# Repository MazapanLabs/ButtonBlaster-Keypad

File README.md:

# ButtonBlaster-Keypad

ButtonBlaster is a compact 48-key keypad based on the Orpheus Pico microcontroller and designed to work with the KMK firmware. The project was inspired by an ergonomic keyboard shown in a video by Joe Scotto. The PCB was custom-designed and paired with a 3D-printed case. It uses Gateron mechanical switches and discrete diodes.

## 🎥 Inspiration

Design inspired by a keyboard featured in a video by Joe Scotto:  
https://youtu.be/sMTs8F6Fk6s?si=EPKrmchUF-LIuJZo

---

## 📦 Specifications

### 🔩 Bill of Materials (BOM)

| Quantity | Component                             | Link                                                                                                     |
|----------|----------------------------------------|----------------------------------------------------------------------------------------------------------|
| 48x      | Gateron KS-3X1 Milky Switch            | [Keychron](https://www.keychron.mx/products/gateron-ks-3x1-milky-switch?variant=45655197909205)         |
| 48x      | Keycaps                                | [Keychron](https://www.keychron.mx/products/keychron-k12-keycap-set?variant=45655109271765)             |
| 48x      | Diodes 1N4148                          | [UElectronics](https://uelectronics.com/producto/kit-de-100-diodos-1n5399-1n5408-1n4148-1n4007-1n5819-1n5822/) |
| 1x       | Orpheus Pico                           | —                                                                                                        |
| 1x       | Custom PCB                             | —                                                                                                        |
| 10x      | M3 brass heatsets                      | [UElectronics](https://uelectronics.com/producto/rosca-de-laton-m2-m3-m4/)                               |
| 10x      | M3x12 screws                           | [MercadoLibre](https://articulo.mercadolibre.com.mx/MLM-3383497816-tornillo-m3-de-cruz-12mm-100pzs-_JM) |

### 🧰 Other files

- Firmware: **KMK**
- STL files:
  - `ButtonBlaster-Keypad_Top.stl`
  - `ButtonBlaster-Keypad_Bottom.stl`

---

## 📷 Project Images

### 🔌 Schematic

### 🧠 PCB

### 🧱 Case

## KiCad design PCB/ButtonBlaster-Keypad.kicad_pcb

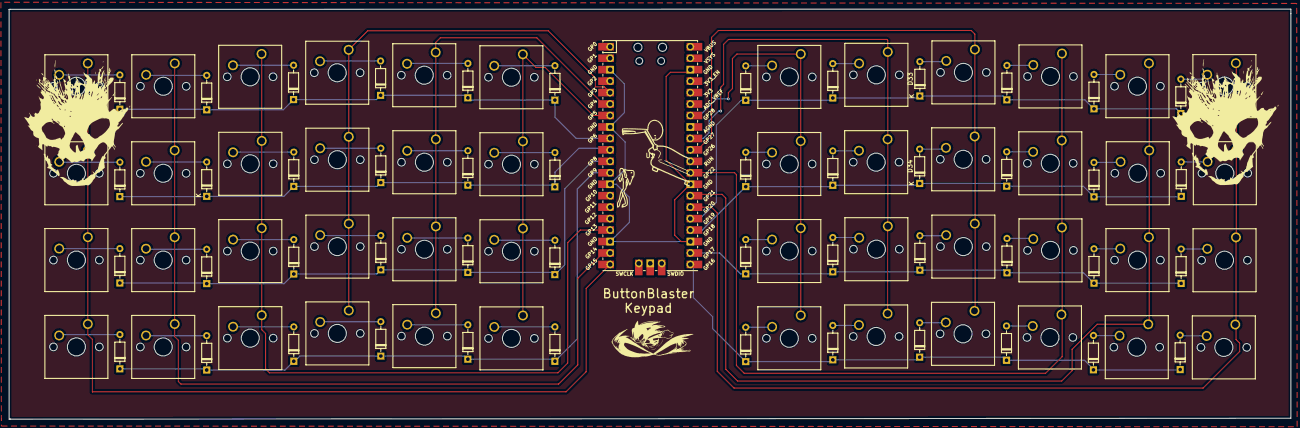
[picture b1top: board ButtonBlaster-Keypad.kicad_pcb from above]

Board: 2 copper layers, 284.1 x 90.9 mm, 97 parts (0 on the bottom side), 69 nets.

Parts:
A1: SW_Push; SW_Cherry_MX_1.00u_PCB
ALT1: SW_Push; SW_Cherry_MX_1.00u_PCB
Abajo1: SW_Push; SW_Cherry_MX_1.00u_PCB
AltGR1: SW_Push; SW_Cherry_MX_1.00u_PCB
Arriba1: SW_Push; SW_Cherry_MX_1.00u_PCB
B1: SW_Push; SW_Cherry_MX_1.00u_PCB
C1: SW_Push; SW_Cherry_MX_1.00u_PCB
CTRL1: SW_Push; SW_Cherry_MX_1.00u_PCB
D1, D2, D3, D4, D5, D6, D7, D8, D9, D10, D11, D12, D13, D14, D15, D16, D17, D18, D19, D20, D21, D22, D23, D24, D25, D26, D27, D28, D29, D30, D31, D32, D33, D34, D35, D36, D37, D38, D39, D40, D41, D42, D43, D44, D45, D46, D47, D48: 1N4148; D_DO-35_SOD27_P7.62mm_Horizontal
De1: SW_Push; SW_Cherry_MX_1.00u_PCB
Delete1: SW_Push; SW_Cherry_MX_1.00u_PCB
Derecha1: SW_Push; SW_Cherry_MX_1.00u_PCB
E1: SW_Push; SW_Cherry_MX_1.00u_PCB
Enter1: SW_Push; SW_Cherry_MX_1.00u_PCB
Esc1: SW_Push; SW_Cherry_MX_1.00u_PCB
Espacio1, Espacio2: SW_Push; SW_Cherry_MX_1.00u_PCB
F1: SW_Push; SW_Cherry_MX_1.00u_PCB
FN1: SW_Push; SW_Cherry_MX_1.00u_PCB
G1: SW_Push; SW_Cherry_MX_1.00u_PCB
H1: SW_Push; SW_Cherry_MX_1.00u_PCB
I1: SW_Push; SW_Cherry_MX_1.00u_PCB
Izquierda1: SW_Push; SW_Cherry_MX_1.00u_PCB
J1: SW_Push; SW_Cherry_MX_1.00u_PCB
K1: SW_Push; SW_Cherry_MX_1.00u_PCB
L1: SW_Push; SW_Cherry_MX_1.00u_PCB
Loquesea1, Loquesea2, Loquesea3, Loquesea4: SW_Push; SW_Cherry_MX_1.00u_PCB
M1: SW_Push; SW_Cherry_MX_1.00u_PCB
Mayus1: SW_Push; SW_Cherry_MX_1.00u_PCB
N1: SW_Push; SW_Cherry_MX_1.00u_PCB
O1: SW_Push; SW_Cherry_MX_1.00u_PCB
P1: SW_Push; SW_Cherry_MX_1.00u_PCB
Q1: SW_Push; SW_Cherry_MX_1.00u_PCB
R1: SW_Push; SW_Cherry_MX_1.00u_PCB
S1: SW_Push; SW_Cherry_MX_1.00u_PCB
ShiftL1: SW_Push; SW_Cherry_MX_1.00u_PCB
T1: SW_Push; SW_Cherry_MX_1.00u_PCB
TAB1: SW_Push; SW_Cherry_MX_1.00u_PCB
U1: Pico; RPi_Pico_SMD_TH
U2: SW_Push; SW_Cherry_MX_1.00u_PCB
V1: SW_Push; SW_Cherry_MX_1.00u_PCB
W1: SW_Push; SW_Cherry_MX_1.00u_PCB
Win1: SW_Push; SW_Cherry_MX_1.00u_PCB
X1: SW_Push; SW_Cherry_MX_1.00u_PCB
Y1: SW_Push; SW_Cherry_MX_1.00u_PCB
Z1: SW_Push; SW_Cherry_MX_1.00u_PCB
Ñ1: SW_Push; SW_Cherry_MX_1.00u_PCB

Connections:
C1A: Loquesea1.1, Mayus1.1, ShiftL1.1, TAB1.1, U1.20 (GPIO15)
C1B: Espacio2.1, H1.1, N1.1, U1.34 (GPIO28_ADC2), Y1.1
C2A: A1.1, CTRL1.1, Q1.1, U1.19 (GPIO14), Z1.1
C2B: AltGR1.1, J1.1, M1.1, U1.32 (GPIO27_ADC1), U2.1
C3A: FN1.1, S1.1, U1.17 (GPIO13), W1.1, X1.1
C3B: I1.1, K1.1, Loquesea2.1, Loquesea3.1, U1.31 (GPIO26_ADC0)
C4A: C1.1, De1.1, E1.1, U1.5 (GPIO3), Win1.1
C4B: Izquierda1.1, L1.1, Loquesea4.1, O1.1, U1.29 (GPIO22)
C5A: ALT1.1, F1.1, R1.1, U1.6 (GPIO4), V1.1
C5B: Abajo1.1, Arriba1.1, P1.1, U1.27 (GPIO21), Ñ1.1
C6A: B1.1, Espacio1.1, G1.1, T1.1, U1.7 (GPIO5)
C6B: Delete1.1, Derecha1.1, Enter1.1, Esc1.1, U1.26 (GPIO20)
F1A: D1.1 (K), D5.1 (K), D9.1 (K), D13.1 (K), D17.1 (K), D21.1 (K), U1.9 (GPIO6)
F1B: D25.1 (K), D29.1 (K), D33.1 (K), D37.1 (K), D41.1 (K), D45.1 (K), U1.25 (GPIO19)
F2A: D2.1 (K), D6.1 (K), D10.1 (K), D14.1 (K), D18.1 (K), D22.1 (K), U1.10 (GPIO7)
F2B: D26.1 (K), D30.1 (K), D34.1 (K), D38.1 (K), D42.1 (K), D46.1 (K), U1.24 (GPIO18)
F3A: D3.1 (K), D7.1 (K), D11.1 (K), D15.1 (K), D19.1 (K), D23.1 (K), U1.11 (GPIO8)
F3B: D27.1 (K), D31.1 (K), D35.1 (K), D39.1 (K), D43.1 (K), D47.1 (K), U1.22 (GPIO17)
F4A: D4.1 (K), D8.1 (K), D12.1 (K), D16.1 (K), D20.1 (K), D24.1 (K), U1.12 (GPIO9)
F4B: D28.1 (K), D32.1 (K), D36.1 (K), D40.1 (K), D44.1 (K), D48.1 (K), U1.21 (GPIO16)
GND: U1.3 (GND), U1.8 (GND), U1.13 (GND), U1.18 (GND), U1.23 (GND), U1.28 (GND), U1.38 (GND)
unnamed: D1.2 (A), TAB1.2
unnamed: D2.2 (A), Mayus1.2
unnamed: D3.2 (A), ShiftL1.2
unnamed: D4.2 (A), Loquesea1.2
unnamed: D5.2 (A), Q1.2
unnamed: A1.2, D6.2 (A)
unnamed: D7.2 (A), Z1.2
unnamed: CTRL1.2, D8.2 (A)
unnamed: D9.2 (A), W1.2
unnamed: D10.2 (A), S1.2
unnamed: D11.2 (A), X1.2
unnamed: D12.2 (A), FN1.2
unnamed: D13.2 (A), E1.2
unnamed: D14.2 (A), De1.2
unnamed: C1.2, D15.2 (A)
unnamed: D16.2 (A), Win1.2
unnamed: D17.2 (A), R1.2
unnamed: D18.2 (A), F1.2
unnamed: D19.2 (A), V1.2
unnamed: ALT1.2, D20.2 (A)
unnamed: D21.2 (A), T1.2
unnamed: D22.2 (A), G1.2
unnamed: B1.2, D23.2 (A)
unnamed: D24.2 (A), Espacio1.2
unnamed: D25.2 (A), Y1.2
unnamed: D26.2 (A), H1.2
unnamed: D27.2 (A), N1.2
unnamed: D28.2 (A), Espacio2.2
unnamed: D29.2 (A), U2.2
unnamed: D30.2 (A), J1.2
unnamed: D31.2 (A), M1.2
unnamed: AltGR1.2, D32.2 (A)
unnamed: D33.2 (A), I1.2
unnamed: D34.2 (A), K1.2
unnamed: D35.2 (A), Loquesea2.2
unnamed: D36.2 (A), Loquesea3.2
unnamed: D37.2 (A), O1.2
unnamed: D38.2 (A), L1.2
unnamed: D39.2 (A), Loquesea4.2
unnamed: D40.2 (A), Izquierda1.2
unnamed: D41.2 (A), P1.2
unnamed: D42.2 (A), Ñ1.2
unnamed: Arriba1.2, D43.2 (A)
unnamed: Abajo1.2, D44.2 (A)
unnamed: D45.2 (A), Esc1.2
unnamed: D46.2 (A), Delete1.2
unnamed: D47.2 (A), Enter1.2
unnamed: D48.2 (A), Derecha1.2

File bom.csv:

Designator,Footprint,Quantity,Value,LCSC Part #
"A1, ABAJO1, ALT1, ALTGR1, ARRIBA1, B1, C1, CTRL1, DE1, DELETE1, DERECHA1, E1, ENTER1, ESC1, ESPACIO1, ESPACIO2, F1, FN1, G1, H1, I1, IZQUIERDA1, J1, K1, L1, LOQUESEA1, LOQUESEA2, LOQUESEA3, LOQUESEA4, M1, MAYUS1, N1, O1, P1, Q1, R1, S1, SHIFTL1, T1, TAB1, U2, V1, W1, WIN1, X1, Y1, Z1, Ñ1",SW_Cherry_MX_1.00u_PCB,48,SW_Push,
"D1, D10, D11, D12, D13, D14, D15, D16, D17, D18, D19, D2, D20, D21, D22, D23, D24, D25, D26, D27, D28, D29, D3, D30, D31, D32, D33, D34, D35, D36, D37, D38, D39, D4, D40, D41, D42, D43, D44, D45, D46, D47, D48, D5, D6, D7, D8, D9",D_DO-35_SOD27_P7.62mm_Horizontal,48,1N4148,
U1,RPi_Pico_SMD_TH,1,Pico,

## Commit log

2025-02-21 Create a
2025-02-23 Rename Bottom.png to BottomF.png
2025-02-23 Rename Top.png to TopF.png
